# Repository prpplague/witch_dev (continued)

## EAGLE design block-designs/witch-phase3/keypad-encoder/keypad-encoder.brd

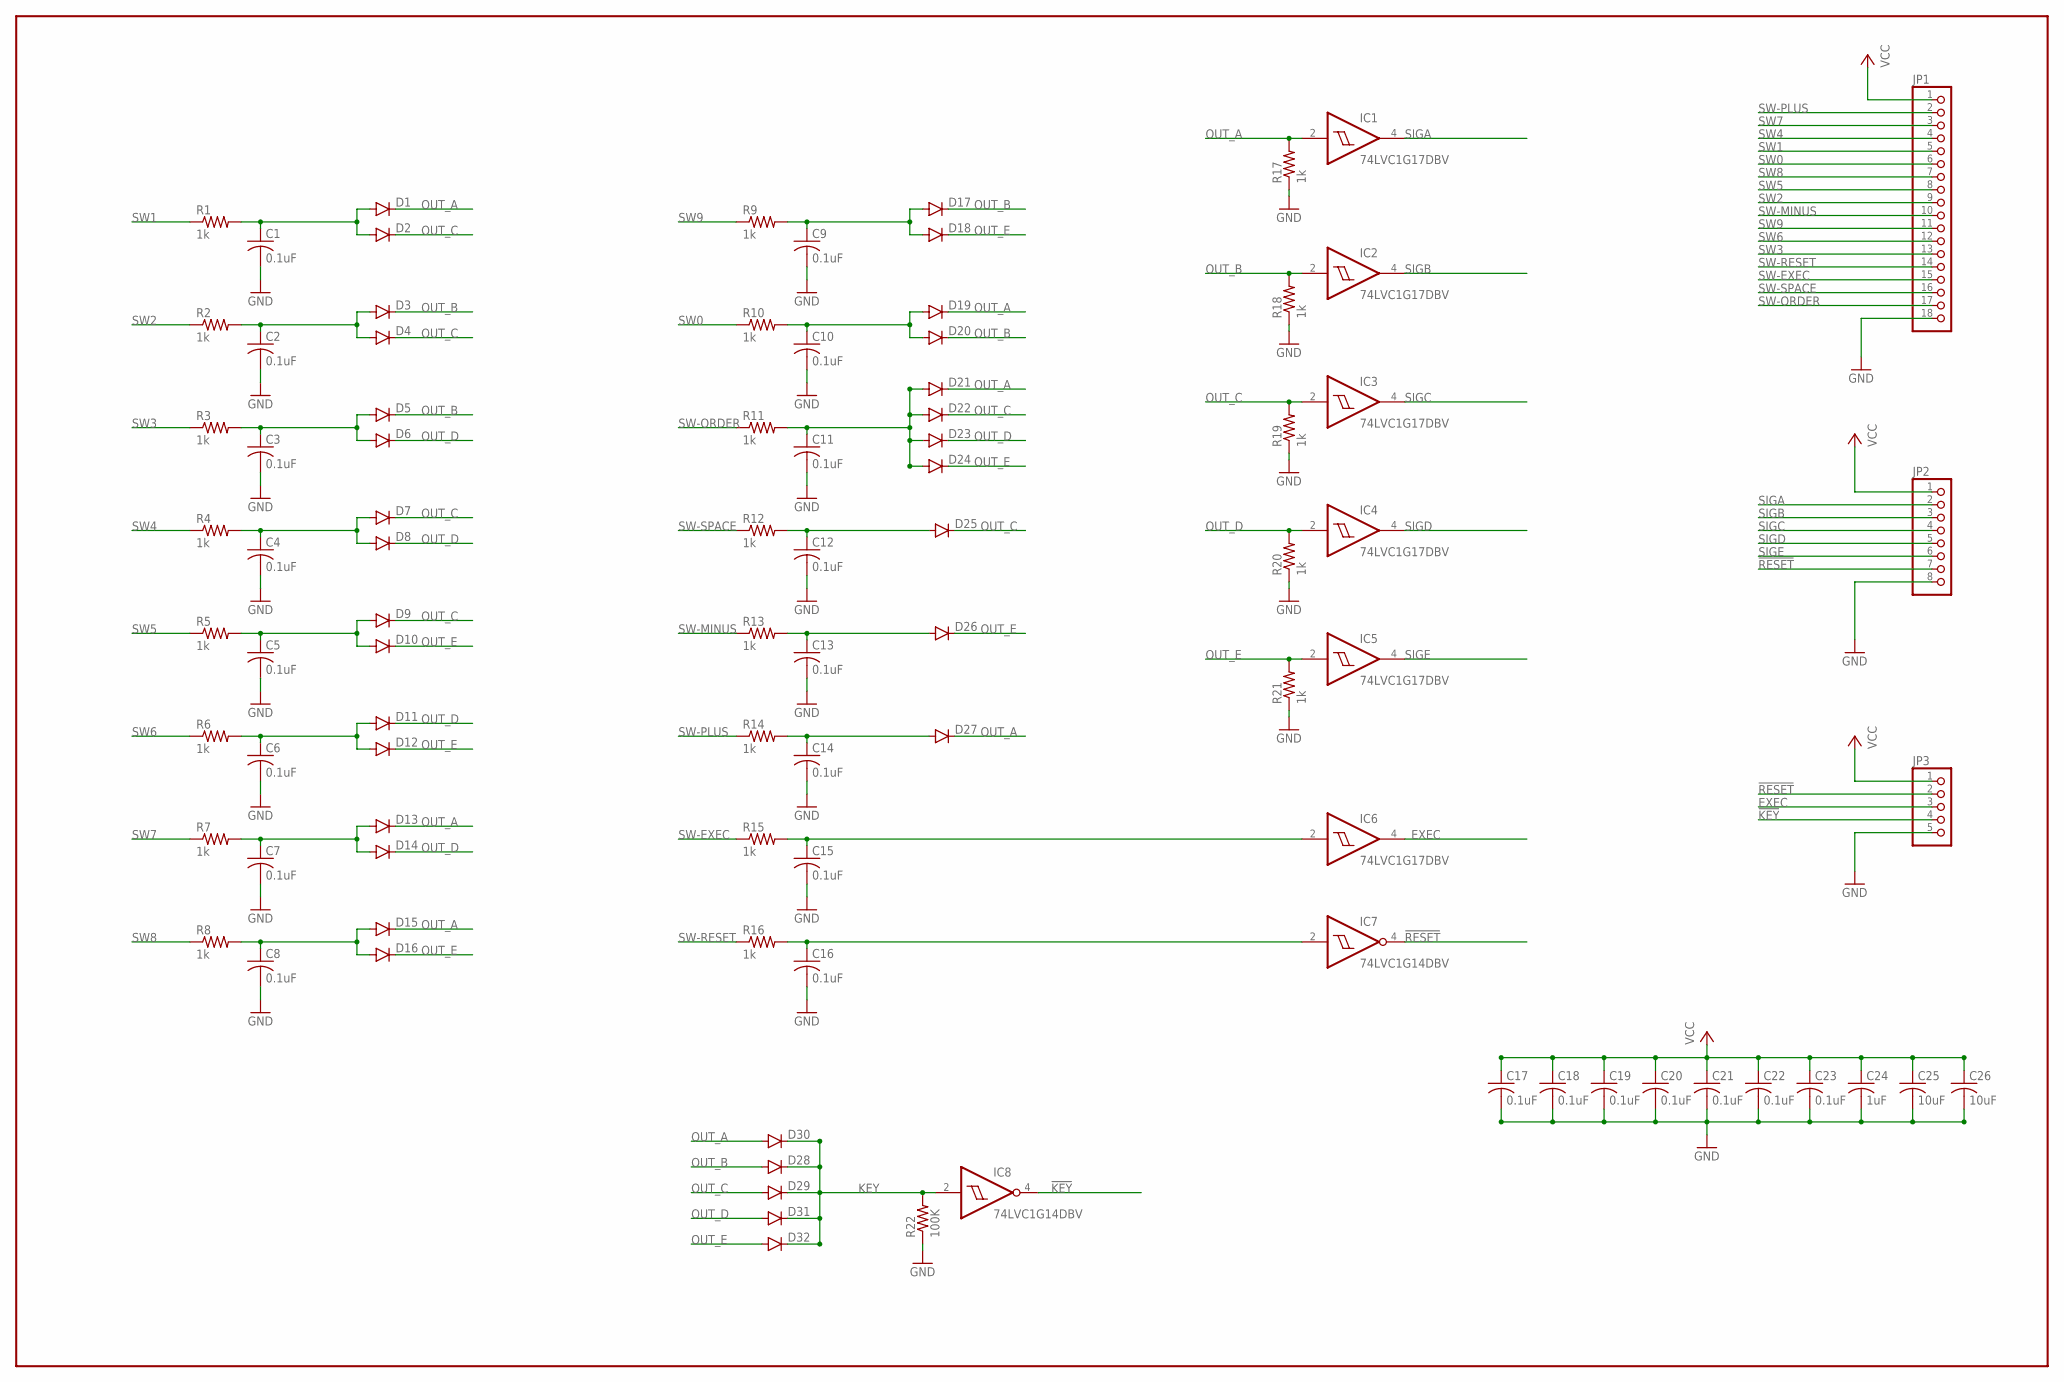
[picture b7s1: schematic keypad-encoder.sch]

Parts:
C1, C2, C3, C4, C5, C6, C7, C8, C9, C10, C11, C12, C13, C14, C15, C16, C17, C18, C19, C20, C21, C22, C23: 0.1uF; C0805
C24: 1uF; C0805
C25, C26: 10uF; C0805
D1, D2, D3, D4, D5, D6, D7, D8, D9, D10, D11, D12, D13, D14, D15, D16, D17, D18, D19, D20, D21, D22, D23, D24, D25, D26, D27, D28, D29, D30, D31, D32: DIODEPTH; DIODE-1N4001
IC1, IC2, IC3, IC4, IC5, IC6: 74LVC1G17DBV; SOT23-5
IC7, IC8: 74LVC1G14DBV; SOT23-5
JP1: PINHD-1X18; 1X18
JP2: PINHD-1X8; 1X08
JP3: PINHD-1X5; 1X05
R1, R2, R3, R4, R5, R6, R7, R8, R9, R10, R11, R12, R13, R14, R15, R16, R17, R18, R19, R20, R21: 1k; R0805
R22: 100K; R0805

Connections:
!KEY: IC8.4 (O), JP3.4
!RESET: IC7.4 (O), JP2.7, JP3.2
EXEC: IC6.4 (O), JP3.3
GND: C1.2, C2.2, C3.2, C4.2, C5.2, C6.2, C7.2, C8.2, C9.2, C10.2, C11.2, C12.2, C13.2, C14.2, C15.2, C16.2, C17.2, C18.2, C19.2, C20.2, C21.2, C22.2, C23.2, C24.2, C25.2, C26.2, IC1.3 (GND), IC2.3 (GND), IC3.3 (GND), IC4.3 (GND), IC5.3 (GND), IC6.3 (GND), IC7.3 (GND), IC8.3 (GND), JP1.18, JP2.8, JP3.5, R17.1, R18.1, R19.1, R20.1, R21.1, R22.1
KEY: D28.C, D29.C, D30.C, D31.C, D32.C, IC8.2 (I), R22.2
unnamed: C11.1, D21.A, D22.A, D23.A, D24.A, R11.2
unnamed: C1.1, D1.A, D2.A, R1.2
unnamed: C2.1, D3.A, D4.A, R2.2
unnamed: C3.1, D5.A, D6.A, R3.2
unnamed: C4.1, D7.A, D8.A, R4.2
unnamed: C5.1, D9.A, D10.A, R5.2
unnamed: C6.1, D11.A, D12.A, R6.2
unnamed: C7.1, D13.A, D14.A, R7.2
unnamed: C8.1, D15.A, D16.A, R8.2
unnamed: C9.1, D17.A, D18.A, R9.2
unnamed: C10.1, D19.A, D20.A, R10.2
unnamed: C12.1, D25.A, R12.2
unnamed: C13.1, D26.A, R13.2
unnamed: C14.1, D27.A, R14.2
unnamed: C15.1, IC6.2 (I), R15.2
unnamed: C16.1, IC7.2 (I), R16.2
OUT_A: D1.C, D13.C, D15.C, D19.C, D21.C, D27.C, D30.A, IC1.2 (I), R17.2
OUT_B: D3.C, D5.C, D17.C, D20.C, D28.A, IC2.2 (I), R18.2
OUT_C: D2.C, D4.C, D7.C, D9.C, D22.C, D25.C, D29.A, IC3.2 (I), R19.2
OUT_D: D6.C, D8.C, D11.C, D14.C, D23.C, D31.A, IC4.2 (I), R20.2
OUT_E: D10.C, D12.C, D16.C, D18.C, D24.C, D26.C, D32.A, IC5.2 (I), R21.2
SIGA: IC1.4 (O), JP2.2
SIGB: IC2.4 (O), JP2.3
SIGC: IC3.4 (O), JP2.4
SIGD: IC4.4 (O), JP2.5
SIGE: IC5.4 (O), JP2.6
SW0: JP1.6, R10.1
SW1: JP1.5, R1.1
SW2: JP1.9, R2.1
SW3: JP1.13, R3.1
SW4: JP1.4, R4.1
SW5: JP1.8, R5.1
SW6: JP1.12, R6.1
SW7: JP1.3, R7.1
SW8: JP1.7, R8.1
SW9: JP1.11, R9.1
SW-EXEC: JP1.15, R15.1
SW-MINUS: JP1.10, R13.1
SW-ORDER: JP1.17, R11.1
SW-PLUS: JP1.2, R14.1
SW-RESET: JP1.14, R16.1
SW-SPACE: JP1.16, R12.1
VCC: C17.1, C18.1, C19.1, C20.1, C21.1, C22.1, C23.1, C24.1, C25.1, C26.1, IC1.5 (VCC), IC2.5 (VCC), IC3.5 (VCC), IC4.5 (VCC), IC5.5 (VCC), IC6.5 (VCC), IC7.5 (VCC), IC8.5 (VCC), JP1.1, JP2.1, JP3.1

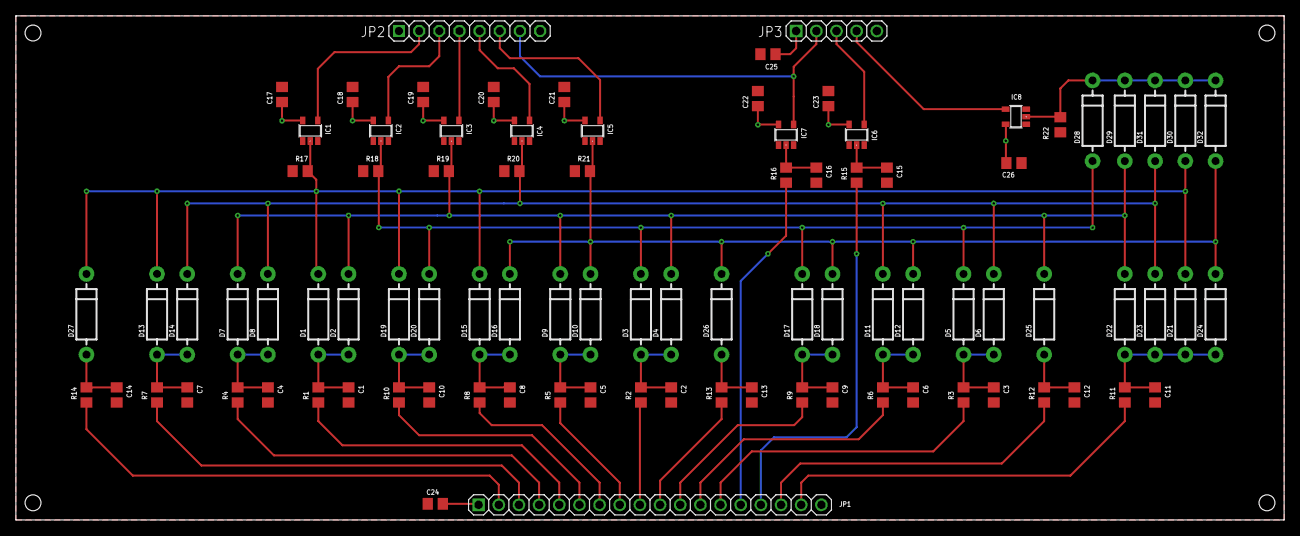
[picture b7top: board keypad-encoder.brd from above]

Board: 2 copper layers, 159.8 x 63.5 mm, 91 parts (0 on the bottom side), 48 nets.

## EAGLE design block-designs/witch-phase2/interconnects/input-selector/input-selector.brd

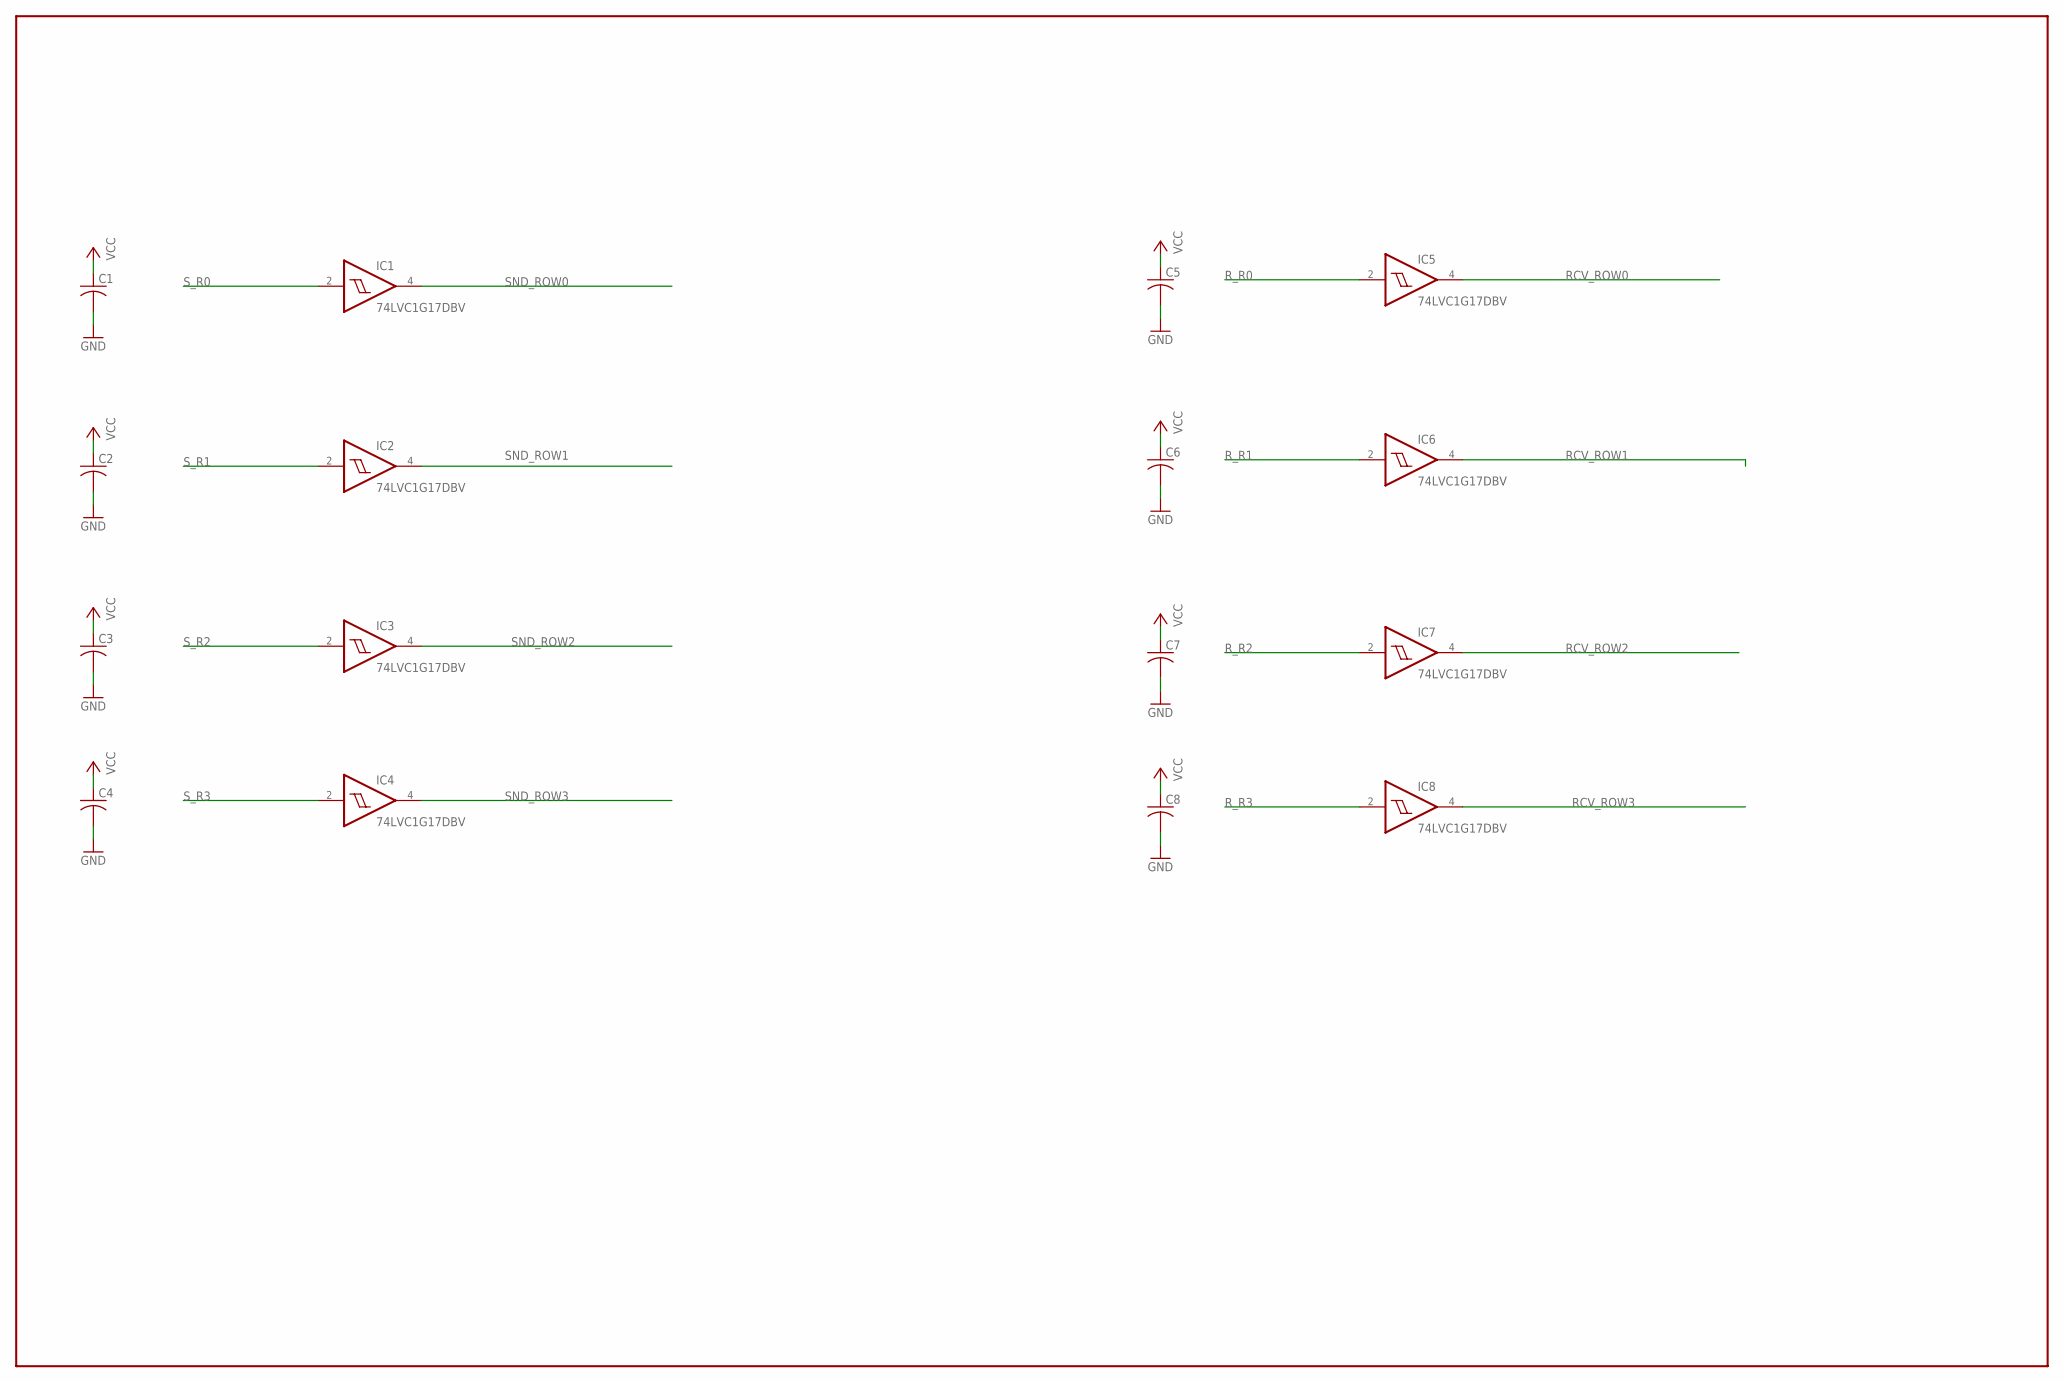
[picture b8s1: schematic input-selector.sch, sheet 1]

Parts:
C1, C2, C3, C4, C5, C6, C7, C8: C-USC0603; C0603
IC1, IC2, IC3, IC4, IC5, IC6, IC7, IC8: 74LVC1G17DBV; SOT23-5

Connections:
GND: C1.2, C2.2, C3.2, C4.2, C5.2, C6.2, C7.2, C8.2, IC1.3 (GND), IC2.3 (GND), IC3.3 (GND), IC4.3 (GND), IC5.3 (GND), IC6.3 (GND), IC7.3 (GND), IC8.3 (GND); also elsewhere on the board
RCV_ROW0: IC5.4 (O); also elsewhere on the board
RCV_ROW1: IC6.4 (O); also elsewhere on the board
RCV_ROW2: IC7.4 (O); also elsewhere on the board
RCV_ROW3: IC8.4 (O); also elsewhere on the board
R_R0: IC5.2 (I); also elsewhere on the board
R_R1: IC6.2 (I); also elsewhere on the board
R_R2: IC7.2 (I); also elsewhere on the board
R_R3: IC8.2 (I); also elsewhere on the board
SND_ROW0: IC1.4 (O); also elsewhere on the board
SND_ROW1: IC2.4 (O); also elsewhere on the board
SND_ROW2: IC3.4 (O); also elsewhere on the board
SND_ROW3: IC4.4 (O); also elsewhere on the board
S_R0: IC1.2 (I); also elsewhere on the board
S_R1: IC2.2 (I); also elsewhere on the board
S_R2: IC3.2 (I); also elsewhere on the board
S_R3: IC4.2 (I); also elsewhere on the board
VCC: C1.1, C2.1, C3.1, C4.1, C5.1, C6.1, C7.1, C8.1, IC1.5 (VCC), IC2.5 (VCC), IC3.5 (VCC), IC4.5 (VCC), IC5.5 (VCC), IC6.5 (VCC), IC7.5 (VCC), IC8.5 (VCC); also elsewhere on the board

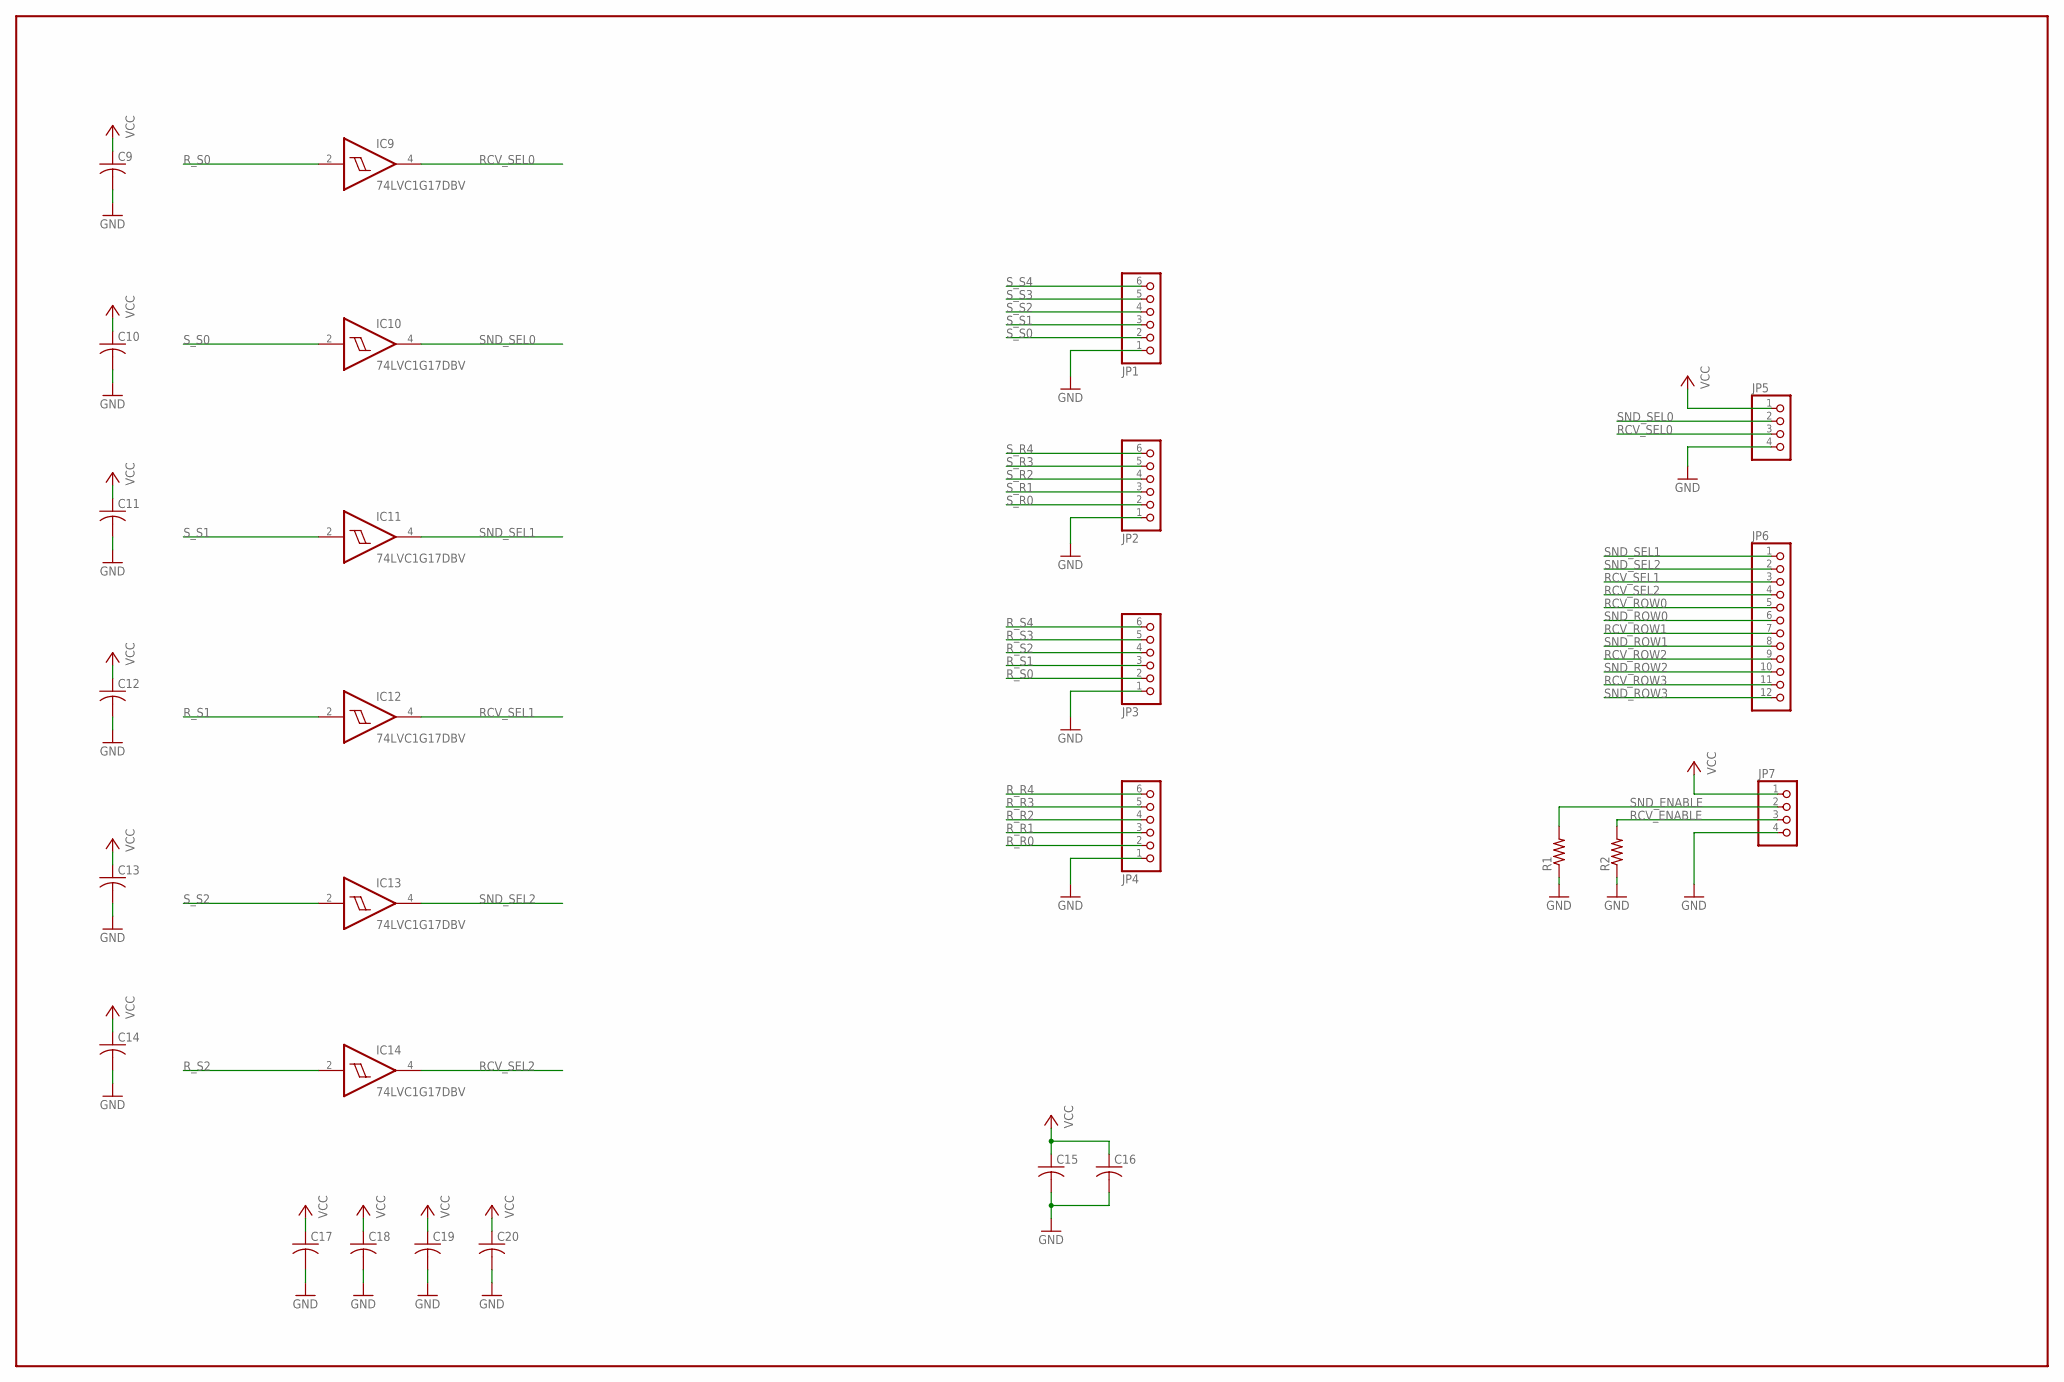
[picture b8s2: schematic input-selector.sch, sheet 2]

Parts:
C9, C10, C11, C12, C13, C14, C17, C18, C19, C20: C-USC0603; C0603
C15, C16: C-USC0805; C0805
IC9, IC10, IC11, IC12, IC13, IC14: 74LVC1G17DBV; SOT23-5
JP1, JP2, JP3, JP4: PINHD-1X6; 1X06
JP5, JP7: PINHD-1X4; 1X04
JP6: PINHD-1X12; 1X12
R1, R2: R-US_R0805; R0805

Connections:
GND: C9.2, C10.2, C11.2, C12.2, C13.2, C14.2, C15.2, C16.2, C17.2, C18.2, C19.2, C20.2, IC9.3 (GND), IC10.3 (GND), IC11.3 (GND), IC12.3 (GND), IC13.3 (GND), IC14.3 (GND), JP1.1, JP2.1, JP3.1, JP4.1, JP5.4, JP7.4, R1.1, R2.1; also elsewhere on the board
RCV_ENABLE: JP7.3, R2.2
RCV_ROW0: JP6.5; also elsewhere on the board
RCV_ROW1: JP6.7; also elsewhere on the board
RCV_ROW2: JP6.9; also elsewhere on the board
RCV_ROW3: JP6.11; also elsewhere on the board
RCV_SEL0: IC9.4 (O), JP5.3
RCV_SEL1: IC12.4 (O), JP6.3
RCV_SEL2: IC14.4 (O), JP6.4
R_R0: JP4.2; also elsewhere on the board
R_R1: JP4.3; also elsewhere on the board
R_R2: JP4.4; also elsewhere on the board
R_R3: JP4.5; also elsewhere on the board
R_R4: JP4.6
R_S0: IC9.2 (I), JP3.2
R_S1: IC12.2 (I), JP3.3
R_S2: IC14.2 (I), JP3.4
R_S3: JP3.5
R_S4: JP3.6
SND_ENABLE: JP7.2, R1.2
SND_ROW0: JP6.6; also elsewhere on the board
SND_ROW1: JP6.8; also elsewhere on the board
SND_ROW2: JP6.10; also elsewhere on the board
SND_ROW3: JP6.12; also elsewhere on the board
SND_SEL0: IC10.4 (O), JP5.2
SND_SEL1: IC11.4 (O), JP6.1
SND_SEL2: IC13.4 (O), JP6.2
S_R0: JP2.2; also elsewhere on the board
S_R1: JP2.3; also elsewhere on the board
S_R2: JP2.4; also elsewhere on the board
S_R3: JP2.5; also elsewhere on the board
S_R4: JP2.6
S_S0: IC10.2 (I), JP1.2
S_S1: IC11.2 (I), JP1.3
S_S2: IC13.2 (I), JP1.4
S_S3: JP1.5
S_S4: JP1.6
VCC: C9.1, C10.1, C11.1, C12.1, C13.1, C14.1, C15.1, C16.1, C17.1, C18.1, C19.1, C20.1, IC9.5 (VCC), IC10.5 (VCC), IC11.5 (VCC), IC12.5 (VCC), IC13.5 (VCC), IC14.5 (VCC), JP5.1, JP7.1; also elsewhere on the board

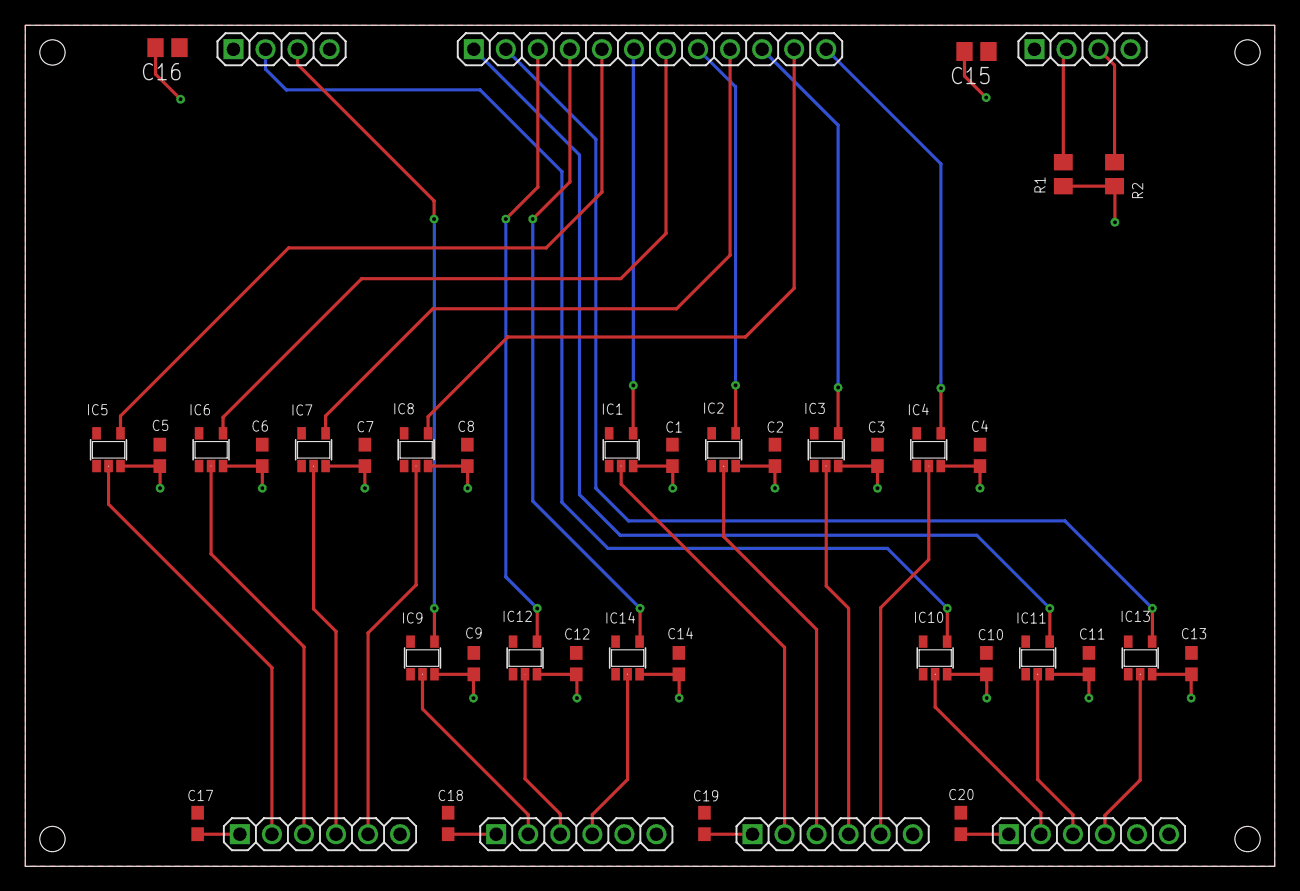
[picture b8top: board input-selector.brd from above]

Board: 2 copper layers, 99.1 x 66.7 mm, 43 parts (0 on the bottom side), 32 nets.

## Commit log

2014-01-22 add initial logic tests
2014-01-22 update readme file with basic info
2014-01-22 update pointers for function call
2014-01-22 correct the logic for dekatron pulse timing
2014-01-23 add documentation directory and some collected files
2014-01-23 test some addition between registers
2014-01-25 updated picture of WITCH
2014-01-25 updated table1
2014-01-26 updated block diagram and dekatron diagram
2014-01-26 minor tweak to the dekatron diagram
2014-01-26 updated fig2
2014-01-30 add new subdirectory for datasheets
2014-01-30 add pdf of Dance's Cold Cathode reference book
2014-01-30 add pdf of programming manual
2014-01-30 add pictures of programming examples
2014-02-07 initial commit of simulated dekatron block design
2014-02-07 add initial design of transfer block
2014-02-13 updated transfer block with board layout
2014-02-20 add images from original scan of EE article
2014-05-13 updated image for fig8
2014-05-13 add datasheet for the cinch-jones 8-pin connectors
2014-05-13 add images of plugin modules
2014-05-13 add webpage and pictures from Matthew Badger
2014-05-22 updated schematics and layouts for phase 1 block designs
2014-05-22 updated files with new images
2014-05-22 add new datasheets and move to upper case naming
2014-05-23 updated dekatron layout
2014-05-23 updated image of dekatron pcb
2014-05-23 add updated image of pulse generator block
2014-05-23 add gerbers for X1 designs
2014-06-03 updated figure 6
2014-06-03 minor tweak to figure 8
2014-06-03 add updated fig8, tweaked fig2
2014-06-03 tweaked fig6
2014-06-03 updated fig6
2014-06-25 add new block design for phase2
2014-06-25 added base schematic
2014-06-30 routed and updated transferboard and add dekatron board
2014-06-30 updated layouts
2014-07-01 sync up
2014-07-01 updated board layouts
2014-07-30 updated figure 4 for the ee article
2014-07-30 new figure 2 with update fonts
2014-08-28 add datasheets and pictures for some tubes
2014-08-28 more datasheets and pictures
2014-08-28 add example programs from TMNOC
2014-09-03 add new figure 7
2014-09-03 add new figure7
2014-09-03 remove lock file
2014-09-04 updated images for fig4, fig6 and fig8
2014-09-04 add the original scans of the article in pdf
2014-10-01 updated pdf schematics
2014-10-02 updated pdf schematics and board files with fixes
2014-10-02 updated images of boards
2014-10-03 updated phase2 image and pdf
2014-10-03 fix pdf for phase2a
2014-10-03 fix phase2b pdf
2014-10-08 updated images and reworked document for 2 column like original
2014-10-08 add references and credits
2014-10-08 minor tweak to caption for witch picture
2014-12-23 minor typo fixes
2015-05-31 add images of cinch-jones connectors
2015-08-06 remove old phase2 tests
2015-08-06 add new phase2 designs
2015-08-06 move phase1 designs into separate subdirectory
2015-08-25 add witch schematics and .gitignore
2015-08-25 add pictures and additional documents
2015-08-25 move pictures of plugin modules under the witch-pictures directory
2015-08-25 remove old software tests
2015-08-28 updated .gitignore to pass on renumber files from eagle
2015-08-28 updated .gitignore to add cam files and gerber subdirectory
2015-08-28 updated revisions with fixes for manufacturing
2015-09-08 add pull down resistors to design
2015-09-13 change pullup to pulldown resistors
2015-09-13 add initial schematic and board layout for transfer block
2015-09-13 initial commit of carry block schematic and board layout
2015-09-14 add OR gate with basic routing
2015-09-14 added carry next and carry previous signals
2015-09-14 updated carry logic
2015-12-03 add initial test code for printing 5-bit pattens on thermal paper
2015-12-03 initial commit of the dot reader sensor board
2015-12-06 add two new oscilloscope captures for the carry unit
2015-12-06 add restoration notes with oscilloscope captures
2015-12-06 add notes on carry unit waveforms
2016-01-19 break the carry section into two pcbs and add new flipflop design
2016-01-20 updated with 74hc195 and carry_oe signal
2016-01-20 remove AND gate and use the Set/Load function
2016-01-20 updated layout
2016-02-21 new block designs for relay set D
2016-02-21 fixes and tweaks for carry block layout
2016-02-21 minor layout tweak
2016-02-21 updated all designs with corrected dimensions and design label
2016-02-23 adjust borders for ground/vcc plains and size to match 1.1inch grids
2016-02-23 updated board layout pictures and pdf schematics
2016-02-28 add cairo printing to code
2016-02-28 add paper size notes
2016-02-28 add simple makefile
2016-03-09 minor tweak to connector location in schematic
2016-03-09 minor tweaks to original large block design
2016-03-09 fixes for the decode - change OR gates to AND gates
2016-03-09 updated for captures
2016-03-09 dot-reader update
2016-03-09 ignore object files
2016-04-18 initial import of the A4 design
2016-06-05 updated designs for new labeling and spacing
2016-06-15 add initial design for mini-store interconnect board
2016-06-15 update .gitignore to include eagle lock files
2016-06-26 add cad files
2016-06-26 add ignore for librecad temp files
2016-07-03 add pictures from TNMOC
2016-07-03 update the interconnect board with spacing and layout changes
2016-07-04 updated design for layout for use with dupont connectors
2016-07-04 update for layout and spacing
2016-07-04 add ignore for temp files
2016-07-04 fix temp file using #
2016-07-04 add cad for transfer block
2016-07-04 add interconnects subdir with transfer-interconnect
2016-07-04 move ministore interconnect to the interconnects subdir
2016-07-04 change name to fit with new naming scheme
2016-08-27 move keyboard tester to new directory for test and debug boards
2016-08-27 minor changes to hole sizes
2016-08-27 add fiducials for pick-and-place
2016-08-27 fixes for layout and connections
2016-08-27 updated to new version of librecad
2016-08-27 add design for mini-store selector
2016-08-27 initial design for pulse generator
2016-08-27 switch position tweaks and drc fixes
2016-08-27 add labels and move downstream power connector
2016-08-28 minor changes to position of reset/run button
2016-08-29 add dekatron sim connector and silkscreen cleanup
2016-09-03 remove connection to pin5 on 555
2016-09-03 fix pin5 on 555, invert 9A latch, connect !RST to TCLK flip-flop
2016-09-16 replace or with d-flipflop to fix zc start issue
2016-09-16 cleanups for readability
2016-09-21 add additional bypass caps and LEDs for signals
2016-09-21 routing tweaks for LEDs
2016-10-31 extensive cleanup of labeling and routing
2016-11-18 update layout with additional caps and change to 0603 passives
2016-11-18 updated layout with additional caps and change to 0603 passives
2016-11-18 updated layout with additional caps and change to 0603 passive. changed clock input to use a 71LVC1G97 configured as AND gate with one input inverted
2016-11-18 initial design for manual input button board
2016-11-18 initial design for manual input switch control
2016-11-18 typo correction
2016-11-19 added caps on the clock lines and switch to 0603 for passives
2016-11-19 switch to using a schmitt trigger with OR gate for clock output
2016-11-26 fix label for IC2
2017-01-22 minor adjustment of designators
2017-01-22 add schmitt-triggers to receive signals
2017-01-22 minor adjustment of reference designators
2017-01-22 add a clock delay breakout board
2017-01-22 add schmitt-trigger breakout board
2017-01-30 add new keypad input board
2017-01-30 updated acrylic layout for smaller 10wide and 15 tall plates
2017-01-30 change polarity of buttons to active high
2017-01-30 new keyboard encoder module
2017-01-30 add new input sequence module
2017-01-31 completed schematic with basic pcb layout
2017-01-31 minor placement tweak
2017-01-31 layout cleanup
2017-01-31 reduced size of module and layout cleanup
2017-01-31 reduce size of module and add mounting holes
2017-01-31 updated labels
2017-02-12 change designs to use non-inverting schmitt triggers
2017-02-14 reduce pcb size, add caps, add LEDs
2017-02-14 add additional logic for zero position bugs
2017-02-14 minor cleanup
2017-02-14 add schmitt trigger to clock output
2017-02-14 add schmitt trigger on the carry output line
2017-02-14 add inverting schmitt trigger to valid data detect output
2017-02-21 update url
2017-02-21 add inverting schemitt trigger for enable line and connect valdata led
2017-02-21 add version of decoder with 0 and 1-9 for future use
2017-02-21 remove 0 and 1-9 special decodes for basic testing
2017-09-22 add resistor values
2017-09-22 updated layout and added inverter for reset signals
2017-09-22 updated layout for easy interface to the rest of the system
2017-09-22 updated layout for easier interfacing
2017-09-22 add component values and manufacturing information
2017-09-22 minor tweaks
2017-09-22 inkjet tests
2017-09-22 updated cad files for new acrylic
2017-09-22 remove pdf files from repo
2017-09-22 add misc pictures and images to documents
2017-09-22 add initial import of shifter register
2017-10-12 rework of cabling for reset, exec, power, and key-up detection
2017-10-12 reference designator cleanup
2017-10-30 update DRC with 12mil min drill size
2017-10-30 rework design: reduced logic to minimum, added 555 timer for debouncing moved encoder connector to top edge of board for easy routing of cabling, changed the pulse-generator connector back to 4-pin f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
2017-11-06 change pull down from 1k to 100k
2017-11-06 change 0.1uF caps from 0805 to 0603
2017-11-06 add new input-selector interconnect board
2017-11-06 schematic cleanup and change bypass caps from 0805 to 0603
2017-11-06 add new connectors for input system and bug fixes from earlier prototype
2017-11-06 pcb layout and labeling cleanup
2017-11-06 add revision numbers
2017-11-13 reorganize boards into correct phase of development
2017-11-13 mv work done on phase3 pulse generator to phase3 directory
2017-11-13 setup move of phase2 pulse generator history
2017-11-13 move shift register to phase4
2017-11-22 updated layout to center connectors
2017-11-22 update schematic and layout for off-by-one error on add/comp clr singals
2017-11-22 add function select LEDs
2017-11-23 add LEDs for functions and tweak layout
2017-11-25 tweak position of function leds
2017-11-25 first cut of a functional dot-reader pcb after changes to 80mm paper
2017-11-25 switch to non-inverting schmitts and layout cleanup
2017-11-25 remove wiring hole
2017-11-26 move 58mm tape reader design to own subdir
2017-11-26 add 80mm tape reader design
2018-03-26 fix QRE1113 pcb footprint and reverse direction of signal labels
2019-06-18 remove eagle schematic file from images directory
